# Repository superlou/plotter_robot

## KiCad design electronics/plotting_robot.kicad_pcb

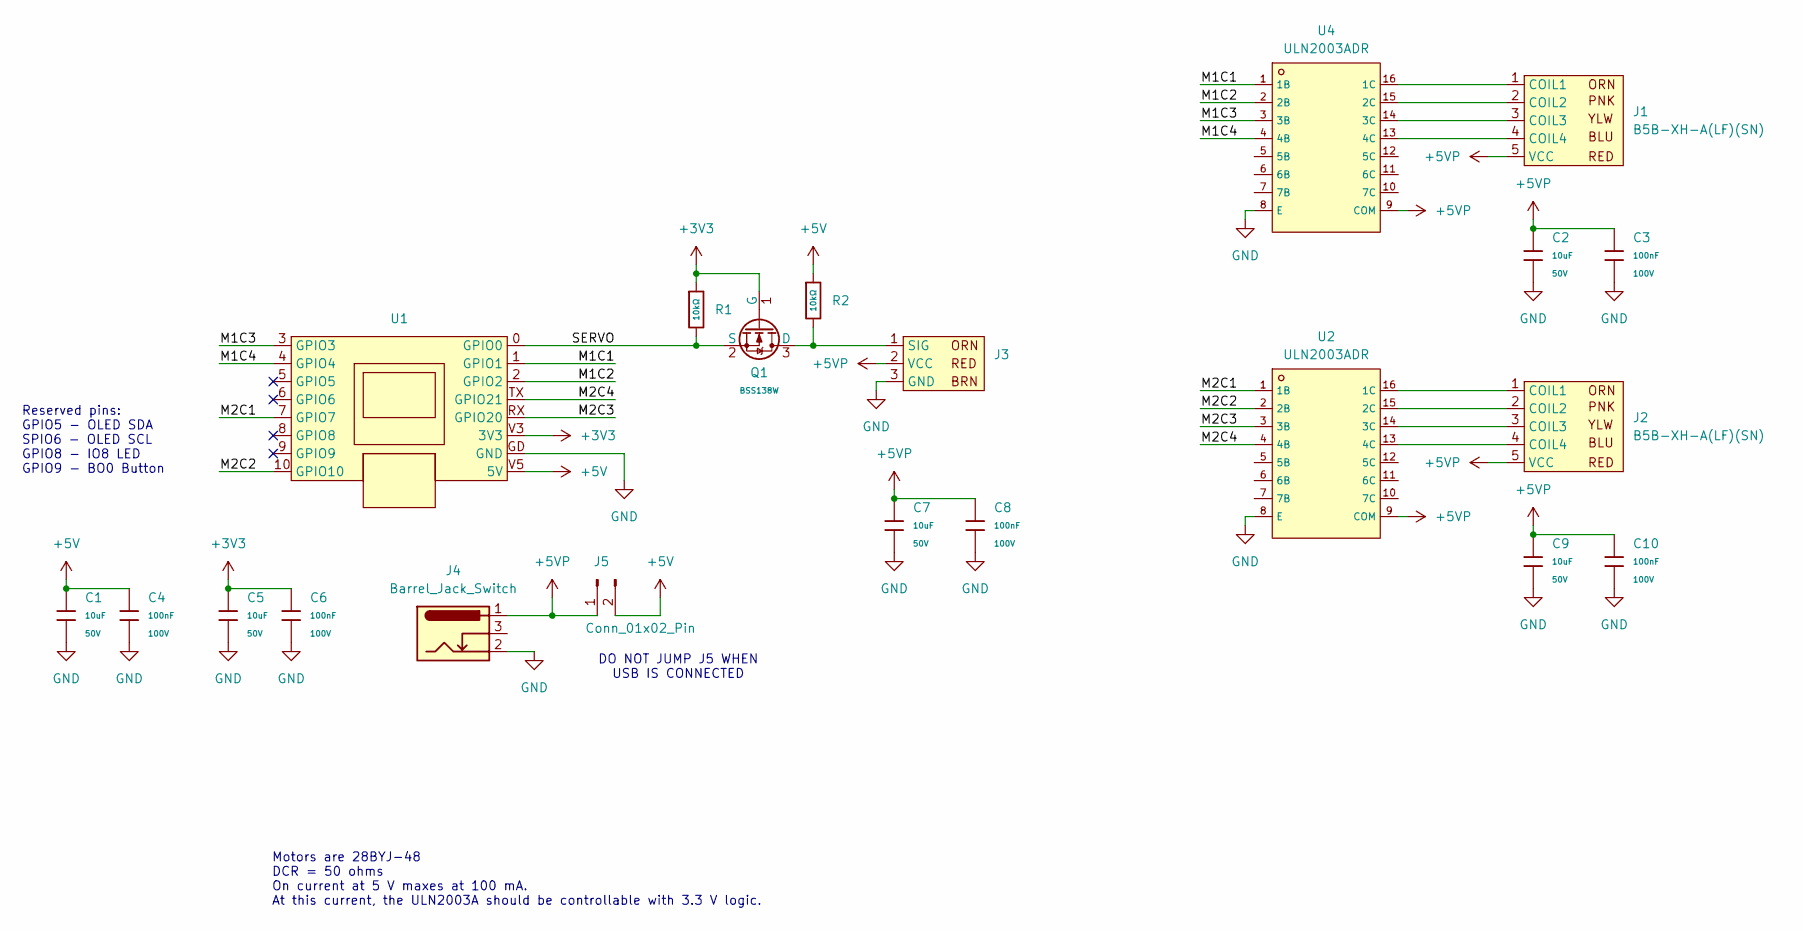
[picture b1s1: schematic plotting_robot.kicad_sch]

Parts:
C1, C2, C5, C7, C9: 10uF; C_1206; Voltage Rated 50V; Tolerance ±10%; Part CL31A106KBHNNNE; LCSC C13585
C3, C4, C6, C8, C10: 100nF; C_0805; Voltage Rated 100V; Tolerance ±10%; Part CL21B104KCFNNNE; LCSC C28233
J1, J2: B5B-XH-A(LF)(SN); JST_EH_B5B-EH-A_1x05_P2.50mm_Vertical; LCSC C157991
J3: PinHeader_1x03_P2.54mm_Vertical
J4: Barrel_Jack_Switch; DC-005
J5: Conn_01x02_Pin; PinHeader_1x02_P2.54mm_Vertical
Q1: BSS138W; Q_SOT-323; Part BSS138W; LCSC C28646265
R1, R2: 10kΩ; R_0805; Overload Voltage (Max) 150V; Tolerance ±1%; Part 0805W8F1002T5E; LCSC C17414
U1: esp32_c3_oled
U2, U4: ULN2003ADR; SOIC-16_L9.9-W3.9-P1.27-LS6.0-BL; Part ULN2003ADR; LCSC C7512

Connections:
+3V3: C5.1, C6.1, Q1.1 (G), R1.1, U1.V3 (3V3); also elsewhere on the board
+5V: C1.1, C4.1, J5.2, R2.1, U1.V5 (5V)
+5VP: C2.1, C3.1, C7.1, C8.1, C9.1, C10.1, J1.5 (VCC), J2.5 (VCC), J3.2 (VCC), J4.1, J5.1, U2.9 (COM), U4.9 (COM)
/M1C1: U1.1 (GPIO1), U4.1 (1B)
/M1C2: U1.2 (GPIO2), U4.2 (2B)
/M1C3: U1.3 (GPIO3), U4.3 (3B)
/M1C4: U1.4 (GPIO4), U4.4 (4B)
/M2C1: U1.7 (GPIO7), U2.1 (1B)
/M2C2: U1.10 (GPIO10), U2.2 (2B)
/M2C3: U1.RX (GPIO20), U2.3 (3B)
/M2C4: U1.TX (GPIO21), U2.4 (4B)
/SERVO: Q1.2 (S), R1.2, U1.0 (GPIO0); also elsewhere on the board
GND: C1.2, C2.2, C3.2, C4.2, C5.2, C6.2, C7.2, C8.2, C9.2, C10.2, J3.3 (GND), J4.2, U1.GD (GND), U2.8 (E), U4.8 (E)
unnamed: J1.1 (COIL1), U4.16 (1C)
unnamed: J1.2 (COIL2), U4.15 (2C)
unnamed: J1.3 (COIL3), U4.14 (3C)
unnamed: J1.4 (COIL4), U4.13 (4C)
unnamed: J2.1 (COIL1), U2.16 (1C)
unnamed: J2.2 (COIL2), U2.15 (2C)
unnamed: J2.3 (COIL3), U2.14 (3C)
unnamed: J2.4 (COIL4), U2.13 (4C)
unnamed 21: J3.1 (SIG), Q1.3 (D), R2.2; also elsewhere on the board

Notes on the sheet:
Motors are 28BYJ-48 DCR = 50 ohms On current at 5 V maxes at 100 mA. At this current, the ULN2003A should be controllable with 3.3 V logic.
Reserved pins: GPIO5 - OLED SDA SPIO6 - OLED SCL GPIO8 - IO8 LED GPIO9 - BO0 Button
DO NOT JUMP J5 WHEN USB IS CONNECTED

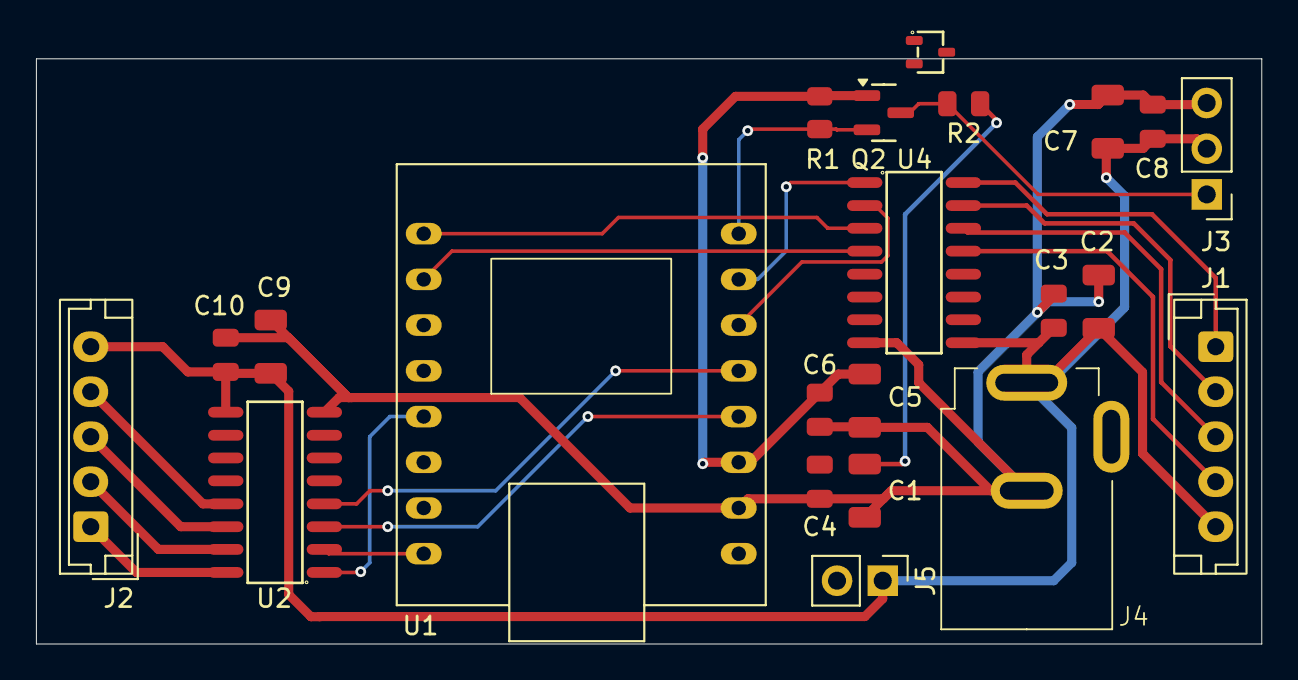
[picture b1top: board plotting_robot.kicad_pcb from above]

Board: 2 copper layers, 68.1 x 32.5 mm, 22 parts (0 on the bottom side), 22 nets.

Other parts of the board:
Q2: BSS138; Q_SOT-23

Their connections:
+3V3: Q2.1 (G); also elsewhere on the board
/SERVO: Q2.2 (S); also elsewhere on the board
unnamed 21: Q2.3 (D); also elsewhere on the board

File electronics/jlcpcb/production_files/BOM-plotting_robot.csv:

Comment,Designator,Footprint,LCSC,Quantity
100nF,"C10,C3,C4,C6,C8",C_0805,C28233,5
10kΩ,"R1,R2",R_0805,C17414,2
10uF,"C1,C2,C5,C7,C9",C_1206,C13585,5
B5B-XH-A(LF)(SN),"J1,J2",JST_EH_B5B-EH-A_1x05_P2.50mm_Vertical,C157991,2
BSS138,Q2,Q_SOT-23,C7420339,1
ULN2003ADR,"U2,U4",SOIC-16_L9.9-W3.9-P1.27-LS6.0-BL,C7512,2
~,J3,PinHeader_1x03_P2.54mm_Vertical,,1
Barrel_Jack_Switch,J4,DC-005,,1
Conn_01x02_Pin,J5,PinHeader_1x02_P2.54mm_Vertical,,1
~,U1,esp32_c3_oled,,1

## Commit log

2026-03-16 Sort of ok, but constraint problems
2026-03-16 Closer
2026-03-23 Initial garbage layout
2026-03-23 Trying to get all JLPCB components
